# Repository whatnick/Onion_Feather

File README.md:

View this project on [CADLAB.io](https://cadlab.io/project/23183). 

# Onion-Omega 2 - Feather Adapter
Adapter board adding much needed USB , Lipo , ADC's etc to Onion-Omega form factor and converting it to an Adafruit Feather

## Renders

**Top Render**

**Bottom Render**

## Roadmap Features
- USB-Serial adapter on-board for direct access to Onion Serial port - [CP2102](https://au.mouser.com/ProductDetail/Silicon-Labs/CP2102N-A02-GQFN20?qs=sGAEpiMZZMtv%252Bwxsgy%2FhiN7Hc8YFqmm37POrUy82J6M%3D)
- [3.3v](http://www.ti.com/product/TPS63001) and [5v](http://www.ti.com/product/TPS63002) power rails with buck-boost converters and power-path IC's
- USB host to expose the Onion USB pins and add USB devices
- Power OR from VUSB and VBAT using Dual Common Cathode Schottky - [PMEG4010CPA,115](https://au.mouser.com/ProductDetail/Nexperia/PMEG4010CPA115?qs=O%2F7ihdSJpea%252BrtmRoPSGEg%3D%3D)
- Ethernet jack with built-in or external pulse transformer - [Amphenol](https://au.mouser.com/ProductDetail/Amphenol-Commercial-Products/RJMG1BD3B8K1ANR?qs=sGAEpiMZZMvQhAhQbXdbBiMgfamRpqKNbIBUiXXy1v4%3D) or [Hanrun](https://www.snapeda.com/parts/HR911105A/DFRobot/view-part/?ref=search&t=HR911105A)
- Battery charger and buck-boost converter - [BQ25895](http://www.ti.com/product/BQ25895)
- 8-channel I2C ADC for the ADC pins - [AD7997](https://www.analog.com/en/products/ad7997.html#product-overview)
- 2-channel I2C ADC for the ADC pins - [MAX11646EUA+](https://au.mouser.com/new/maxim-integrated/maxim-max11646-max11647/) with other Analog pins services by [Onion PCM/PWM](https://docs.onion.io/omega2-docs/generating-pwm-signals.html) pins.
- Dense 20 pin 1.0 mm pitch board-to-wire connector for all pins - [Molex 203566-2007](https://au.mouser.com/ProductDetail/Molex/203566-2007?qs=sGAEpiMZZMs%252BGHln7q6pm8Vn94ktop%2FJB3denez338oFsDPiNVR1nA%3D%3D)
- Qwiic format JST-SH I2C bus connector - [Qwiic](https://www.sparkfun.com/qwiic)
- USB-host protection using [STF202](https://www.onsemi.com/pub/Collateral/STF202-22T1-D.PDF)
- SPI Bus isolation using [74HC367](https://www.ti.com/lit/ds/symlink/sn74hc367.pdf?ts=1601076323582) hex non-inverting tri-state buffer. This can also be used for I2C bus isolation and driving in later revisions using the left over x2 tristate buffers.

## Reference Prior Art
- [Adafruit ESP32 Huzzah Feather](https://github.com/adafruit/Adafruit-HUZZAH32-ESP32-Feather-PCB)
- [BQ25895 Breakout](https://www.bernebeer.nl/new-bq25895-breakout/)
- [Qwiic Featherwing](https://github.com/hongselectronics/Qwiic_Featherwing)

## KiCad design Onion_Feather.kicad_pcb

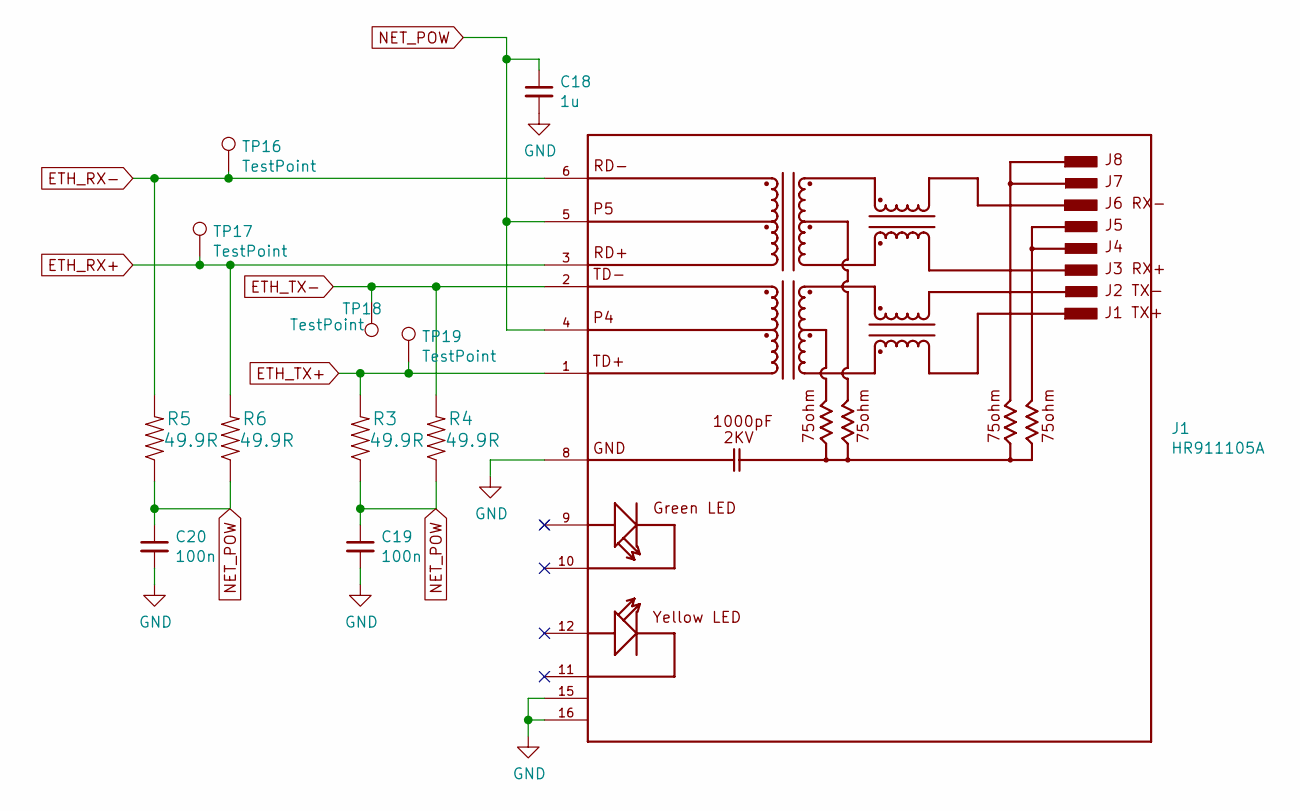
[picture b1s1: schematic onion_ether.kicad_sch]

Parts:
C18: 1u; C_0603_1608Metric
C19, C20: 100n; C_0603_1608Metric
J1: HR911105A; HANRUN_HR911105A
R3, R4, R5, R6: 49.9R; R_0603_1608Metric
TP16, TP17, TP18, TP19: TestPoint; TestPoint_Pad_D1.5mm

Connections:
ETH_RX+: J1.3 (RD+), R6.2, TP17.1; also elsewhere on the board
ETH_RX-: J1.6 (RD-), R5.2, TP16.1; also elsewhere on the board
ETH_TX+: J1.1 (TD+), R3.2, TP19.1; also elsewhere on the board
ETH_TX-: J1.2 (TD-), R4.2, TP18.1; also elsewhere on the board
GND: C18.2, C19.2, C20.2, J1.8 (GND), J1.15 (SHIELD), J1.16 (SHIELD); also elsewhere on the board
NET_POW: C18.1, C19.1, C20.1, J1.4, J1.5, R3.1, R4.1, R5.1, R6.1; also elsewhere on the board

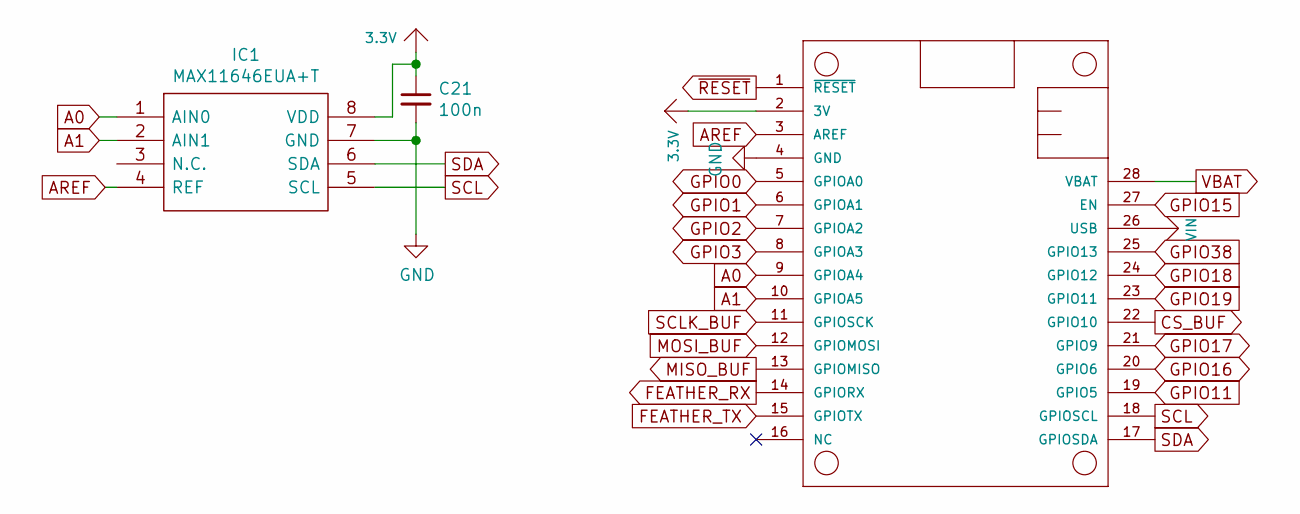
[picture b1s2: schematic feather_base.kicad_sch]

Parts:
C21: 100n; C_0603_1608Metric
IC1: MAX11646EUA+T; TSSOP-8_4.4x3mm_P0.65mm; Manufacturer_Part_Number MAX11646EUA+T; DigiKey Part Number MAX11646EUA+T-ND
MS1: ADAFRUIT_FEATHERWING; adafruit_featherwing

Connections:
3.3V: C21.1, IC1.8 (VDD), MS1.2 (3V); also elsewhere on the board
A0: IC1.1 (AIN0), MS1.9 (GPIOA4)
A1: IC1.2 (AIN1), MS1.10 (GPIOA5)
AREF: IC1.4 (REF), MS1.3 (AREF)
CS_BUF: MS1.22 (GPIO10); also elsewhere on the board
FEATHER_RX: MS1.14 (GPIORX); also elsewhere on the board
FEATHER_TX: MS1.15 (GPIOTX); also elsewhere on the board
GND: C21.2, IC1.7 (GND), MS1.4 (GND); also elsewhere on the board
GPIO0: MS1.5 (GPIOA0); also elsewhere on the board
GPIO1: MS1.6 (GPIOA1); also elsewhere on the board
GPIO2: MS1.7 (GPIOA2); also elsewhere on the board
GPIO3: MS1.8 (GPIOA3); also elsewhere on the board
GPIO11: MS1.19 (GPIO5); also elsewhere on the board
GPIO15: MS1.27 (EN); also elsewhere on the board
GPIO16: MS1.20 (GPIO6); also elsewhere on the board
GPIO17: MS1.21 (GPIO9); also elsewhere on the board
GPIO18: MS1.24 (GPIO12); also elsewhere on the board
GPIO19: MS1.23 (GPIO11); also elsewhere on the board
GPIO38: MS1.25 (GPIO13); also elsewhere on the board
MISO_BUF: MS1.13 (GPIOMISO); also elsewhere on the board
MOSI_BUF: MS1.12 (GPIOMOSI); also elsewhere on the board
SCL: IC1.5 (SCL), MS1.18 (GPIOSCL); also elsewhere on the board
SCLK_BUF: MS1.11 (GPIOSCK); also elsewhere on the board
SDA: IC1.6 (SDA), MS1.17 (GPIOSDA); also elsewhere on the board
VBAT: MS1.28 (VBAT); also elsewhere on the board
VIN: MS1.26 (USB); also elsewhere on the board
~RESET: MS1.1 (~RESET); also elsewhere on the board

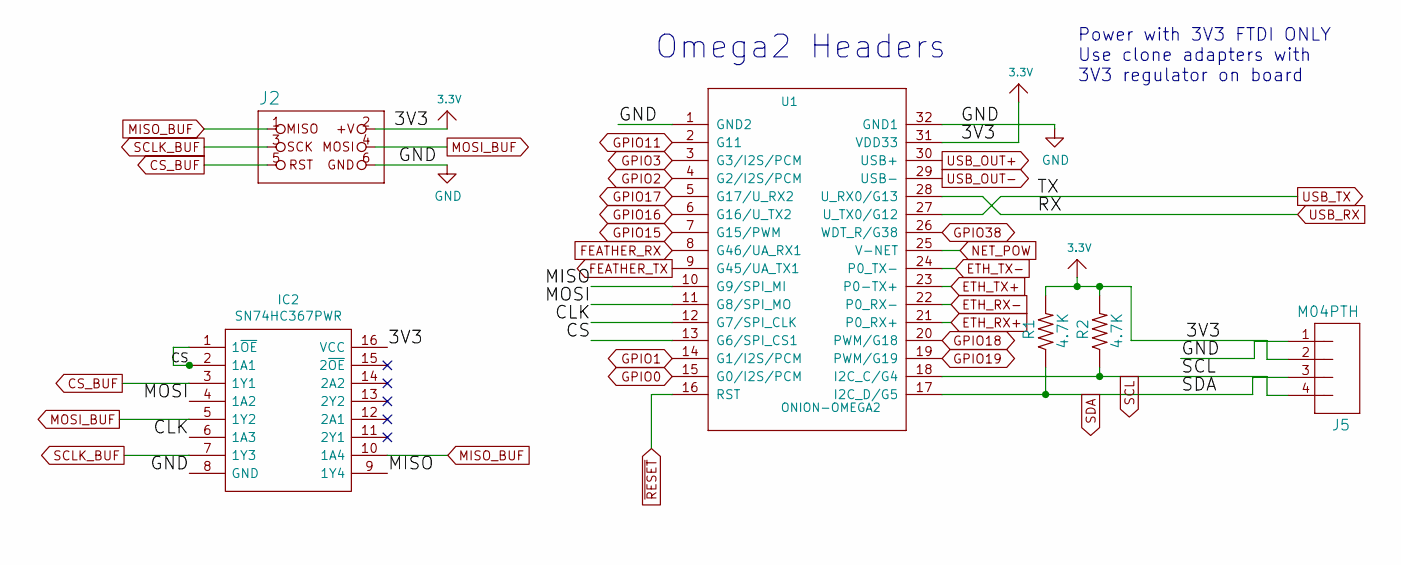
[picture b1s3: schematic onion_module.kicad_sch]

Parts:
IC2: SN74HC367PWR; SOP65P640X120-16N; Mouser Part Number 595-SN74HC367PWR
J2: CON_HEADER_PRG_AVR_ICSP-PTH; JST_SH_SM06B-SRSS-TB_1x06-1MP_P1.00mm_Horizontal
J5: M04PTH; JST_SH_SM04B-SRSS-TB_1x04-1MP_P1.00mm_Horizontal
R1, R2: 4.7K; R_0603_1608Metric
U1: ONION-OMEGA2; Onion_Omega2+

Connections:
3.3V: IC2.16 (VCC), J2.2 (+V), J5.2, R1.2, R2.2, U1.31 (VDD33); also elsewhere on the board
/OnionModule/CLK: IC2.6 (1A3), U1.12 (G7/SPI_CLK)
/OnionModule/CS: IC2.1 (1~OE), IC2.2 (1A1), U1.13 (G6/SPI_CS1)
/OnionModule/MISO: IC2.9 (1Y4), U1.10 (G9/SPI_MI)
/OnionModule/MOSI: IC2.4 (1A2), U1.11 (G8/SPI_MO)
CS_BUF: IC2.3 (1Y1), J2.5 (RST); also elsewhere on the board
ETH_RX+: U1.21 (P0_RX+); also elsewhere on the board
ETH_RX-: U1.22 (P0_RX-); also elsewhere on the board
ETH_TX+: U1.23 (P0-TX+); also elsewhere on the board
ETH_TX-: U1.24 (P0_TX-); also elsewhere on the board
FEATHER_RX: U1.8 (G46/UA_RX1); also elsewhere on the board
FEATHER_TX: U1.9 (G45/UA_TX1); also elsewhere on the board
GND: IC2.8 (GND), J2.6 (GND), J5.1, U1.1 (GND2), U1.32 (GND1); also elsewhere on the board
GPIO0: U1.15 (G0/I2S/PCM); also elsewhere on the board
GPIO1: U1.14 (G1/I2S/PCM); also elsewhere on the board
GPIO2: U1.4 (G2/I2S/PCM); also elsewhere on the board
GPIO3: U1.3 (G3/I2S/PCM); also elsewhere on the board
GPIO11: U1.2 (G11); also elsewhere on the board
GPIO15: U1.7 (G15/PWM); also elsewhere on the board
GPIO16: U1.6 (G16/U_TX2); also elsewhere on the board
GPIO17: U1.5 (G17/U_RX2); also elsewhere on the board
GPIO18: U1.20 (PWM/G18); also elsewhere on the board
GPIO19: U1.19 (PWM/G19); also elsewhere on the board
GPIO38: U1.26 (WDT_R/G38); also elsewhere on the board
MISO_BUF: IC2.10 (1A4), J2.1 (MISO); also elsewhere on the board
MOSI_BUF: IC2.5 (1Y2), J2.4 (MOSI); also elsewhere on the board
NET_POW: U1.25 (V-NET); also elsewhere on the board
SCL: J5.4, R2.1, U1.18 (I2C_C/G4); also elsewhere on the board
SCLK_BUF: IC2.7 (1Y3), J2.3 (SCK); also elsewhere on the board
SDA: J5.3, R1.1, U1.17 (I2C_D/G5); also elsewhere on the board
USB_OUT+: U1.30 (USB+); also elsewhere on the board
USB_OUT-: U1.29 (USB-); also elsewhere on the board
USB_RX: U1.28 (U_RX0/G13); also elsewhere on the board
USB_TX: U1.27 (U_TX0/G12); also elsewhere on the board
~RESET: U1.16 (RST); also elsewhere on the board

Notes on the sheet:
Omega2 Headers
Power with 3V3 FTDI ONLY Use clone adapters with 3V3 regulator on board

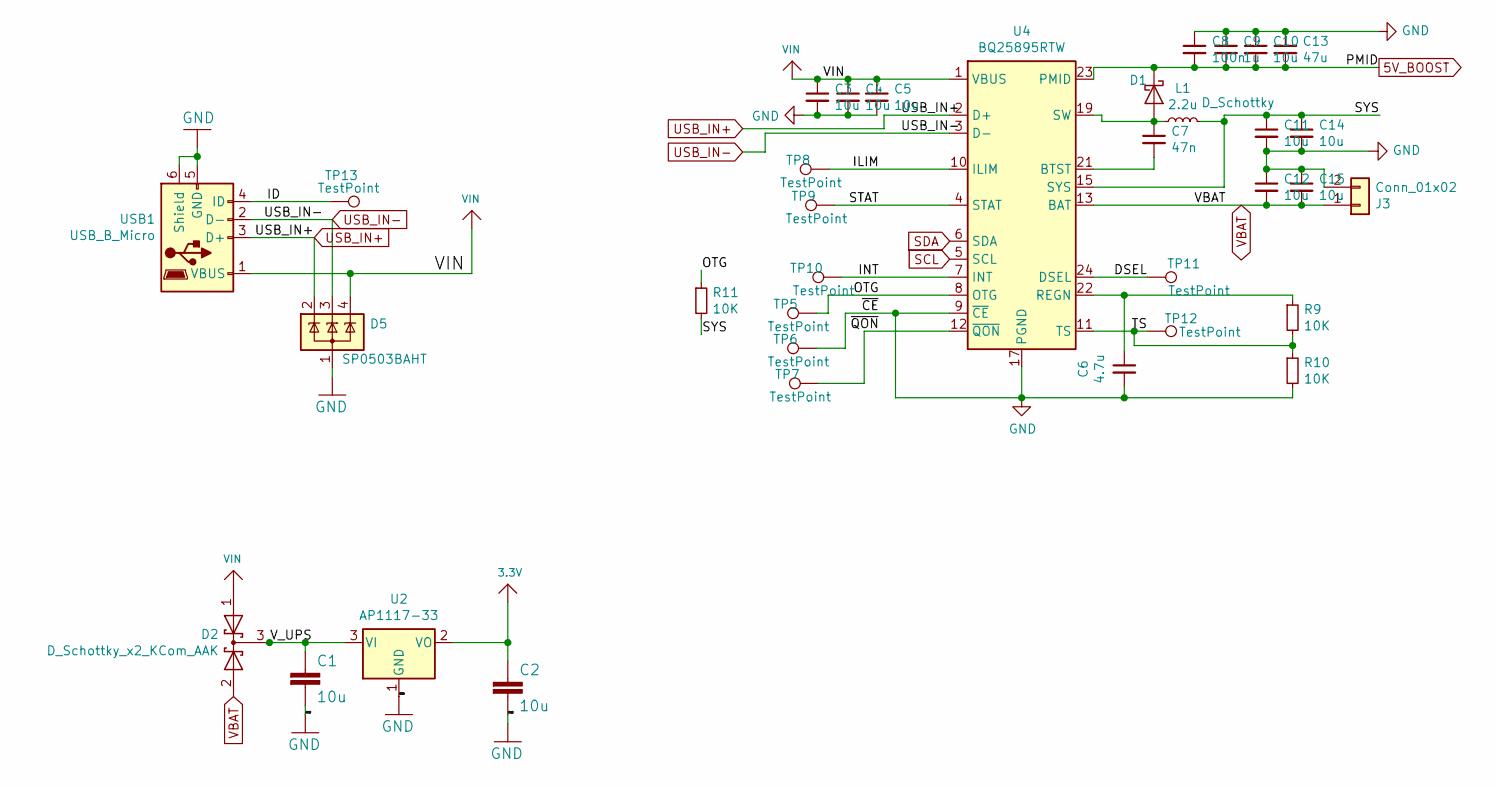
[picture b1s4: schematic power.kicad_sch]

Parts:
C1, C2, C3, C4, C5, C10, C11, C12, C14, C15: 10u; C_0805_2012Metric
C6: 4.7u; C_0805_2012Metric
C7: 47n; C_0603_1608Metric
C8: 100n; C_0603_1608Metric
C9: 1u; C_0603_1608Metric
C13: 47u; C_0805_2012Metric
D1: D_Schottky; D_SOD-123
D2: D_Schottky_x2_KCom_AAK; SOT1061
D5: SP0503BAHT; SOT-143
J3: Conn_01x02; JST_PH_S2B-PH-SM4-TB_1x02-1MP_P2.00mm_Horizontal
L1: 2.2u; L_Coilcraft_XAL5030
R9, R10, R11: 10K; R_0603_1608Metric
TP5, TP6, TP7, TP8, TP9, TP10, TP11, TP12, TP13: TestPoint; TestPoint_Pad_D1.5mm
U2: AP1117-33; SOT-223-3_TabPin2
U4: BQ25895RTW; Texas_S-PWQFN-N24_EP2.7x2.7mm_ThermalVias
USB1: USB_B_Micro; USB_Micro-AB_Molex_47590-0001

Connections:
3.3V: C2.1, U2.2 (VO); also elsewhere on the board
5V_BOOST: C8.2, C9.2, C10.2, C13.2, D1.1 (K), U4.23 (PMID); also elsewhere on the board
/Power Subsystems/DSEL: TP11.1, U4.24 (DSEL)
/Power Subsystems/ID: TP13.1, USB1.4 (ID)
/Power Subsystems/ILIM: TP8.1, U4.10 (ILIM)
/Power Subsystems/INT: TP10.1, U4.7 (INT)
/Power Subsystems/OTG: R11.1, TP5.1, U4.8 (OTG)
/Power Subsystems/STAT: TP9.1, U4.4 (STAT)
/Power Subsystems/SYS: C11.1, C14.1, L1.2, R11.2, U4.15 (SYS), U4.16 (SYS)
/Power Subsystems/TS: R9.2, R10.1, TP12.1, U4.11 (TS)
/Power Subsystems/V_UPS: C1.1, D2.3 (K), U2.3 (VI)
/Power Subsystems/~CE: TP6.1, U4.9 (~CE)
/Power Subsystems/~QON: TP7.1, U4.12 (~QON)
GND: C1.2, C2.2, C3.2, C4.2, C5.2, C6.2, C8.1, C9.1, C10.1, C11.2, C12.1, C13.1, C14.2, C15.1, D5.1 (A), J3.2, R10.2, U2.1 (GND), U4.17 (PGND), U4.18 (PGND), U4.25 (PGND), USB1.5 (GND), USB1.6 (Shield); also elsewhere on the board
unnamed: C6.1, R9.1, U4.22 (REGN)
unnamed: C7.1, D1.2 (A), L1.1, U4.19 (SW), U4.20 (SW)
unnamed: C7.2, U4.21 (BTST)
SCL: U4.5 (SCL); also elsewhere on the board
SDA: U4.6 (SDA); also elsewhere on the board
USB_IN+: D5.2 (K), U4.2 (D+), USB1.3 (D+); also elsewhere on the board
USB_IN-: D5.3 (K), U4.3 (D-), USB1.2 (D-); also elsewhere on the board
VBAT: C12.2, C15.2, D2.2 (A), J3.1, U4.13 (BAT), U4.14 (BAT); also elsewhere on the board
VIN: C3.1, C4.1, C5.1, D2.1 (A), D5.4 (K), U4.1 (VBUS), USB1.1 (VBUS); also elsewhere on the board

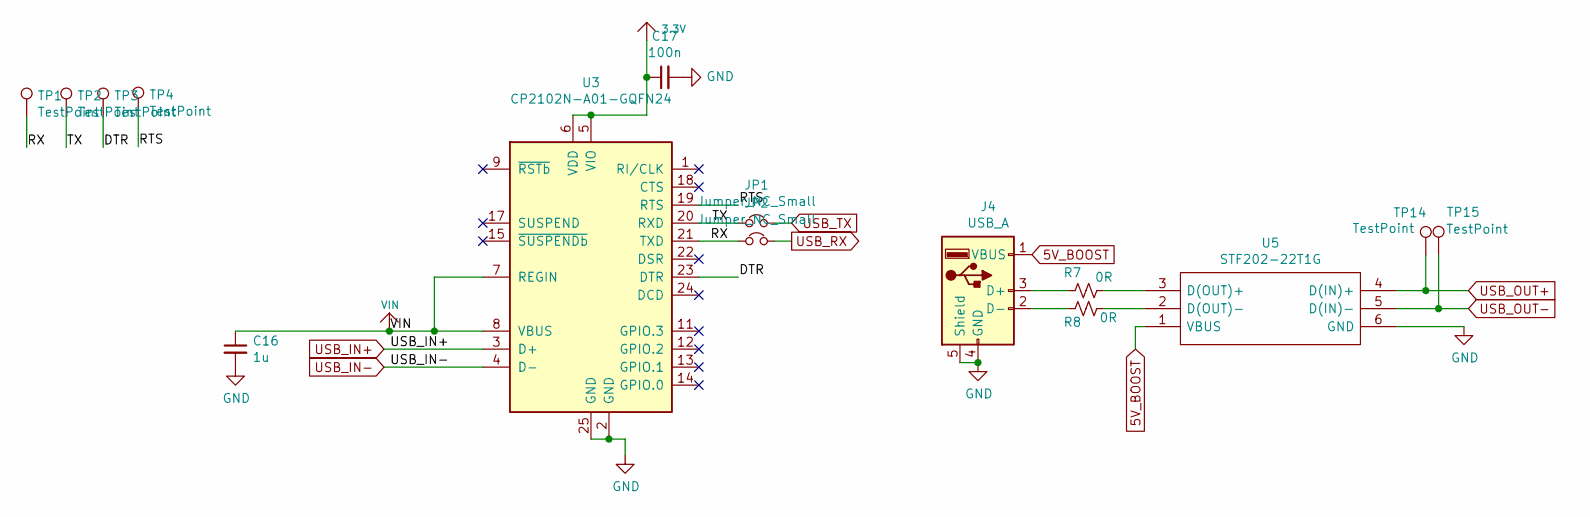
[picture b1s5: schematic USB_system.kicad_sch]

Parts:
C16: 1u; C_0603_1608Metric
C17: 100n; C_0603_1608Metric
J4: USB_A; 67643-0910
JP1, JP2: Jumper_NC_Small; SolderJumper-2_P1.3mm_Bridged_RoundedPad1.0x1.5mm
R7, R8: 0R; R_0603_1608Metric
TP1, TP2, TP3, TP4, TP14, TP15: TestPoint; TestPoint_Pad_D1.5mm
U3: CP2102N-A01-GQFN24; QFN-24-1EP_4x4mm_P0.5mm_EP2.6x2.6mm
U5: STF202-22T1G; SOT95P275X110-6N; Manufacturer_Part_Number STF202-22T1G; Mouser Part Number 863-STF202-22T1G

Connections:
3.3V: C17.1, U3.5 (VIO), U3.6 (VDD); also elsewhere on the board
5V_BOOST: J4.1 (VBUS), U5.1 (VBUS); also elsewhere on the board
/USB Interfaces/DTR: TP3.1, U3.23 (DTR)
/USB Interfaces/RTS: TP4.1, U3.19 (RTS)
/USB Interfaces/RX: JP2.1, TP1.1, U3.21 (TXD)
/USB Interfaces/TX: JP1.1, TP2.1, U3.20 (RXD)
GND: C16.2, C17.2, J4.4 (GND), J4.5 (Shield), U3.2 (GND), U3.25 (GND), U5.6 (GND); also elsewhere on the board
unnamed: J4.2 (D-), R8.2
unnamed: J4.3 (D+), R7.2
unnamed: R7.1, U5.3 (D(OUT)+)
unnamed: R8.1, U5.2 (D(OUT)-)
USB_IN+: U3.3 (D+); also elsewhere on the board
USB_IN-: U3.4 (D-); also elsewhere on the board
USB_OUT+: TP14.1, U5.4 (D(IN)+); also elsewhere on the board
USB_OUT-: TP15.1, U5.5 (D(IN)-); also elsewhere on the board
USB_RX: JP2.2; also elsewhere on the board
USB_TX: JP1.2; also elsewhere on the board
VIN: C16.1, U3.7 (REGIN), U3.8 (VBUS); also elsewhere on the board

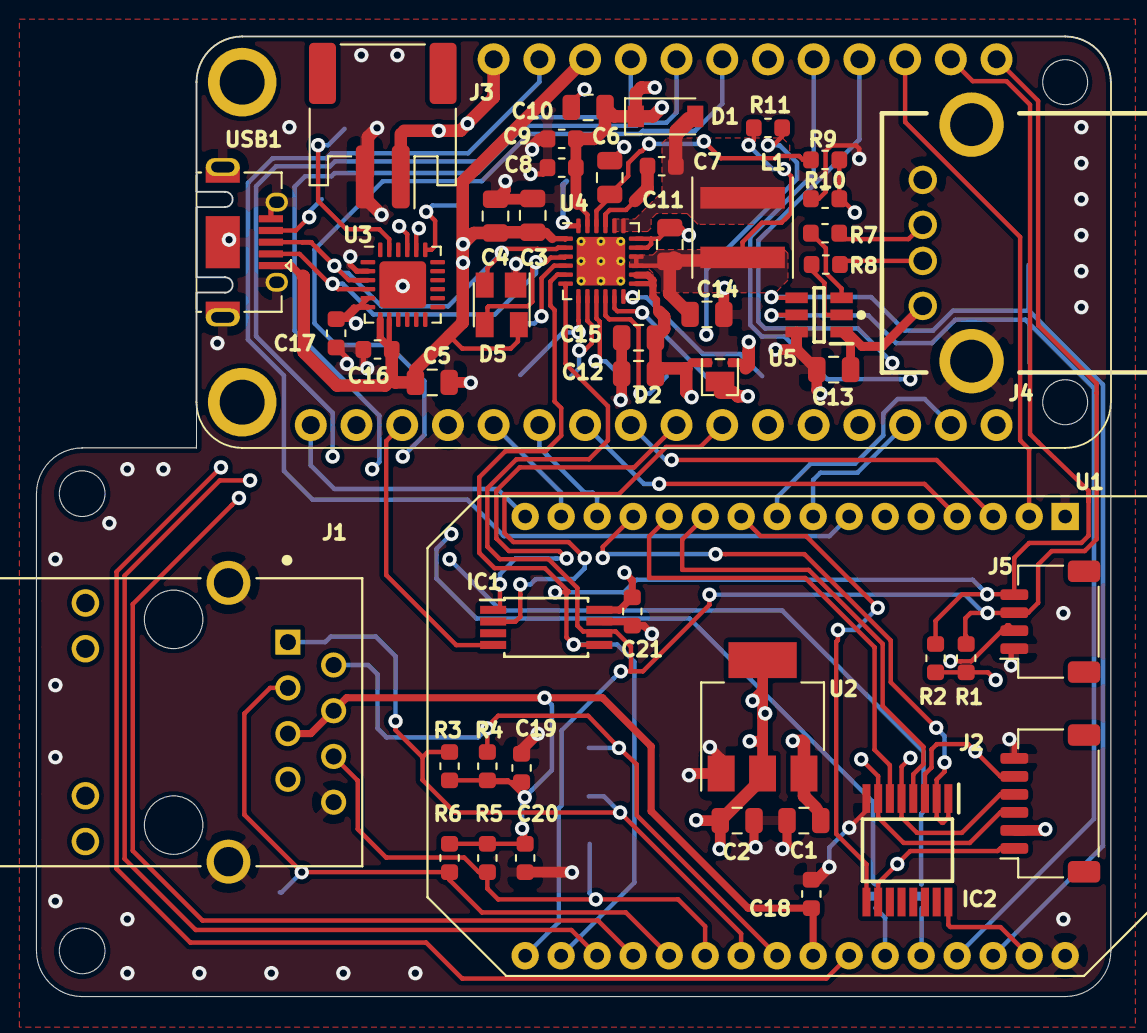
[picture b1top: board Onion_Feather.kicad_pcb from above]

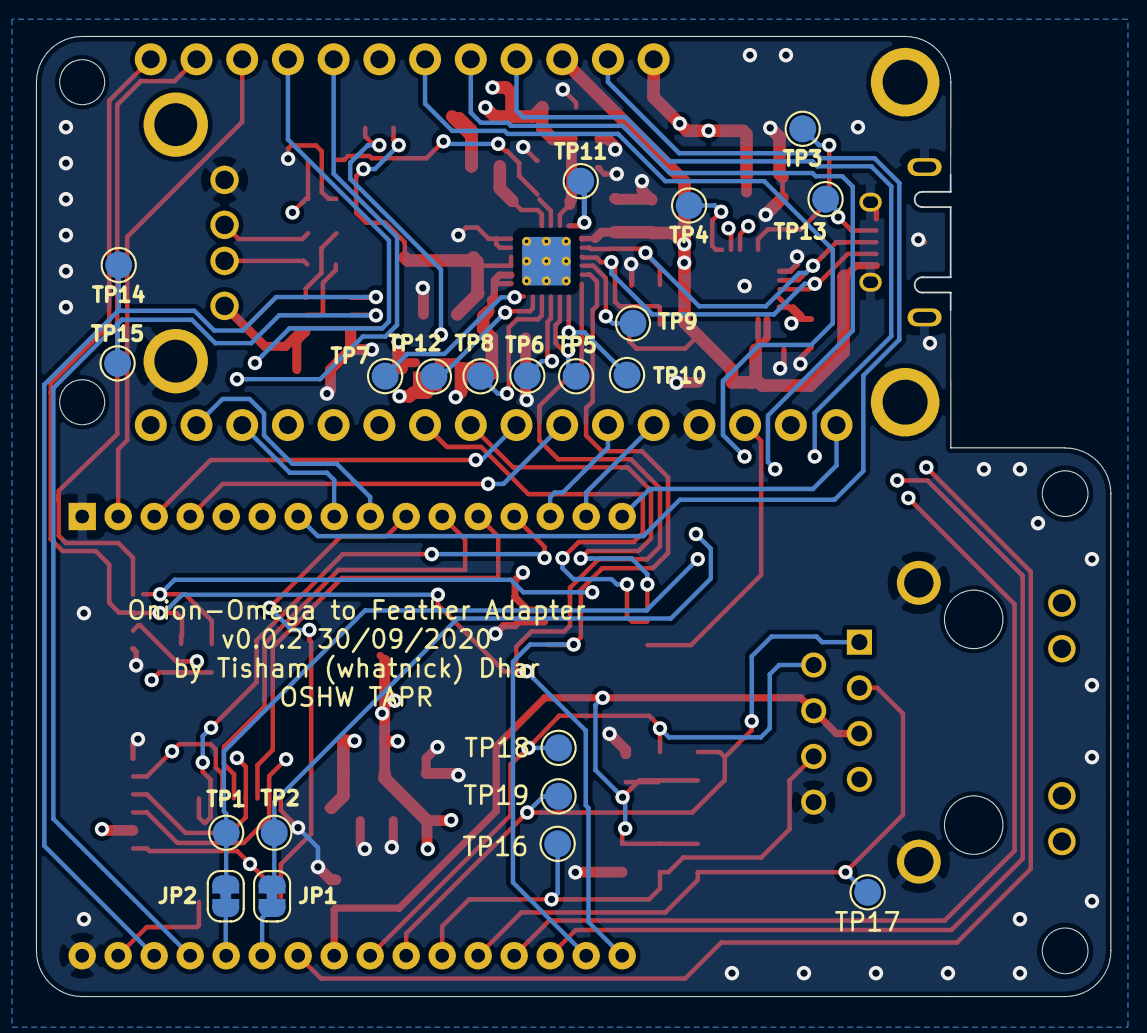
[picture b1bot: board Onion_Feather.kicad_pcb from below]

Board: 4 copper layers, 59.7 x 53.3 mm, 71 parts (21 on the bottom side), 65 nets.

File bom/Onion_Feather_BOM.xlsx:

References | manf# | Value | Footprint | Quantity
C6 | 0805YD475MAT2A | 4.7u | C_0805_2012Metric | 1
C8, C17, C19, C20, C21 | C0603C104M4RAC | 100n | C_0603_1608Metric | 5
C9, C16, C18 | C0603C105M4PAC7411 | 1u | C_0603_1608Metric | 3
C7 | C0603C473M4RACTU | 47n | C_0603_1608Metric | 1
C1, C2, C3, C4, C5, C10, C11, C12, C14, C15 | C0805C106K4PAC | 10u | C_0805_2012Metric | 10
C13 | C0805C476M9PACTU | 47u | C_0805_2012Metric | 1
R9, R10, R11 | CRCW060310K0JNEBC | 10K | R_0603_1608Metric | 3
R7, R8 | MCT0603MZ0000ZP500 | 0R | R_0603_1608Metric | 2
R1, R2 | RT0603DRE074K7L | 4.7K | R_0603_1608Metric | 2
R3, R4, R5, R6 | RT0603FRD0749R9L | 49.9R | R_0603_1608Metric | 4
L1 | XAL5030-222MEC | 2.2u | L_Coilcraft_XAL5030 | 1
D1 | MBR130T3G | D_Schottky | D_SOD-123 | 1
D2 | PMEG4010CPA,115 | D_Schottky_x2_KCom_AAK | SOT1061 | 1
D5 | SP0503BAHTG | SP0503BAHT | SOT-143 | 1
U4 | BQ25895RTW | BQ25895RTW | Texas_S-PWQFN-N24_EP2.7x2.7mm_ThermalVias | 1
U3 | CP2102N-A01-GQFN24R | CP2102N-A01-GQFN24 | QFN-24-1EP_4x4mm_P0.5mm_EP2.6x2.6mm | 1
U5 | STF202-22T1G | STF202-22T1G | SOT95P275X110-6N | 1
U2 | TLV1117-33IDCYR | AP1117-33 | SOT-223-3_TabPin2 | 1
USB1 | 47590-0001 | USB_B_Micro | USB_Micro-AB_Molex_47590-0001 | 1
IC1 | MAX11646EUA+T | MAX11646EUA+T | TSSOP-8_4.4x3mm_P0.65mm | 1
IC2 | SN74HC367PWR | SN74HC367PWR | SOP65P640X120-16N | 1
J4 | 67643-0910 | USB_A | 67643-0910 | 1
J1 | HR911105A | HR911105A | HANRUN_HR911105A | 1
J3 | S2B-PH-SM4-TB(LF)(SN) | Conn_01x02 | JST_PH_S2B-PH-SM4-TB_1x02-1MP_P2.00mm_Horizontal | 1
J5 | SM04B-SRSS-TB(LF)(SN) | M04PTH | JST_SH_SM04B-SRSS-TB_1x04-1MP_P1.00mm_Horizontal | 1
J2 | SM06B-SRSS-TB(LF)(SN) | CON_HEADER_PRG_AVR_ICSP-PTH | JST_SH_SM06B-SRSS-TB_1x06-1MP_P1.00mm_Horizontal | 1

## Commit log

2020-03-03 Initial import
2020-03-07 Add Hanrun magjack
2020-03-07 Try Hanrun magjack on for size
2020-03-07 Importing prior art from Eagle
2020-03-08 Added more features and 3D models
2020-03-29 More wiring
2020-03-29 Get fancy with the battery
2020-03-29 Add WIP render
2020-03-29 Add more to roadmap
2020-04-04 Work on Power and USB-Serial
2020-04-04 Swap pins to use Qwiic spec
2020-04-05 Start making hard choices and wiring GPIO's
2020-04-08 Schematic ready for review
2020-04-09 Add reference to USB protection
2020-04-10 USB protection, schematic Update
2020-04-11 Schematic update
2020-04-12 Schematic and library update, 0 errors
2020-04-17 Routing done
2020-04-18 Add iBOM
2020-04-19 Silkscrenn fix
2020-04-19 PCB update, edge vias
2020-04-20 Add 3d models , silkscreen and renders
2020-04-20 Add some part no.
2020-04-22 Add gerbers and BOM
2020-04-24 Update BOM
2020-06-28 Fix up BOM , add positions for assembly
2020-08-08 Validate i2c devices
2020-08-08 #3 Correct battery connector and align PCB/Schema
2020-08-08 Backlink to CADLAB.io has been added.
2020-08-09 Add battery charger driver
2020-08-09 Some small tweaks
2020-08-09 Try no ILIM
2020-08-11 #6 Fix CE and TS pins
2020-08-12 Note proposed power OR schottky
2020-08-12 WIP on diode OR
2020-08-13 Enable cycle flag to switch BATFET
2020-08-13 Complete sentences in README
2020-08-14 Use common cathode and reroute
2020-08-16 #5 Enable OTG in system config
2020-09-19 #5 Add OTG bias and clean up courtyard
2020-09-20 Start on sparkfun button
2020-09-20 Support multiple buttons and LED
2020-09-21 Add notes to install python3-spidev
2020-09-22 #7 Add tri-state buffer
2020-09-26 #7 Wire in tristate buffer
2020-09-27 #7 Re-route with tristate buffer
2020-09-27 #8 Fix broken USB filter symbol and rewire
2020-09-27 #8 Re-route USB filter
2020-09-29 #9 Add some testpoints for ethernet
2020-09-30 #9 Tie center pin to NET_POW
2020-09-30 New manufacture files
2020-11-17 Support oled and spelling
2020-11-17 Add oled sample
2020-11-17 Change message on OLED
2020-12-01 Move to KiCAD nightly
